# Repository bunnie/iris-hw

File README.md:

# IRIS CAD files

This repository contains IRIS CAD files not found elsewhere.

In particular, the base machine is the [Jubilee3D](https://jubilee3d.com/index.php?title=Main_Page); please refer to its [github](https://github.com/machineagency/jubilee) for its base CAD files.

## About IRIS

This repository is part of the IRIS project, an effort to make it easier to verify the construction of silicon chips.

Read more about IRIS at our [arXiv paper](https://arxiv.org/abs/2303.07406), or the latest [project update](https://www.bunniestudios.com/blog/?p=6937).

## Acknowledgements

This work was funded in part by NLnet’s [NGI0 Entrust](https://nlnet.nl/entrust/) fund, established with support from the European Commission’s Next Generation Internet Program, and my [Github Sponsors](https://github.com/sponsors/bunnie/).

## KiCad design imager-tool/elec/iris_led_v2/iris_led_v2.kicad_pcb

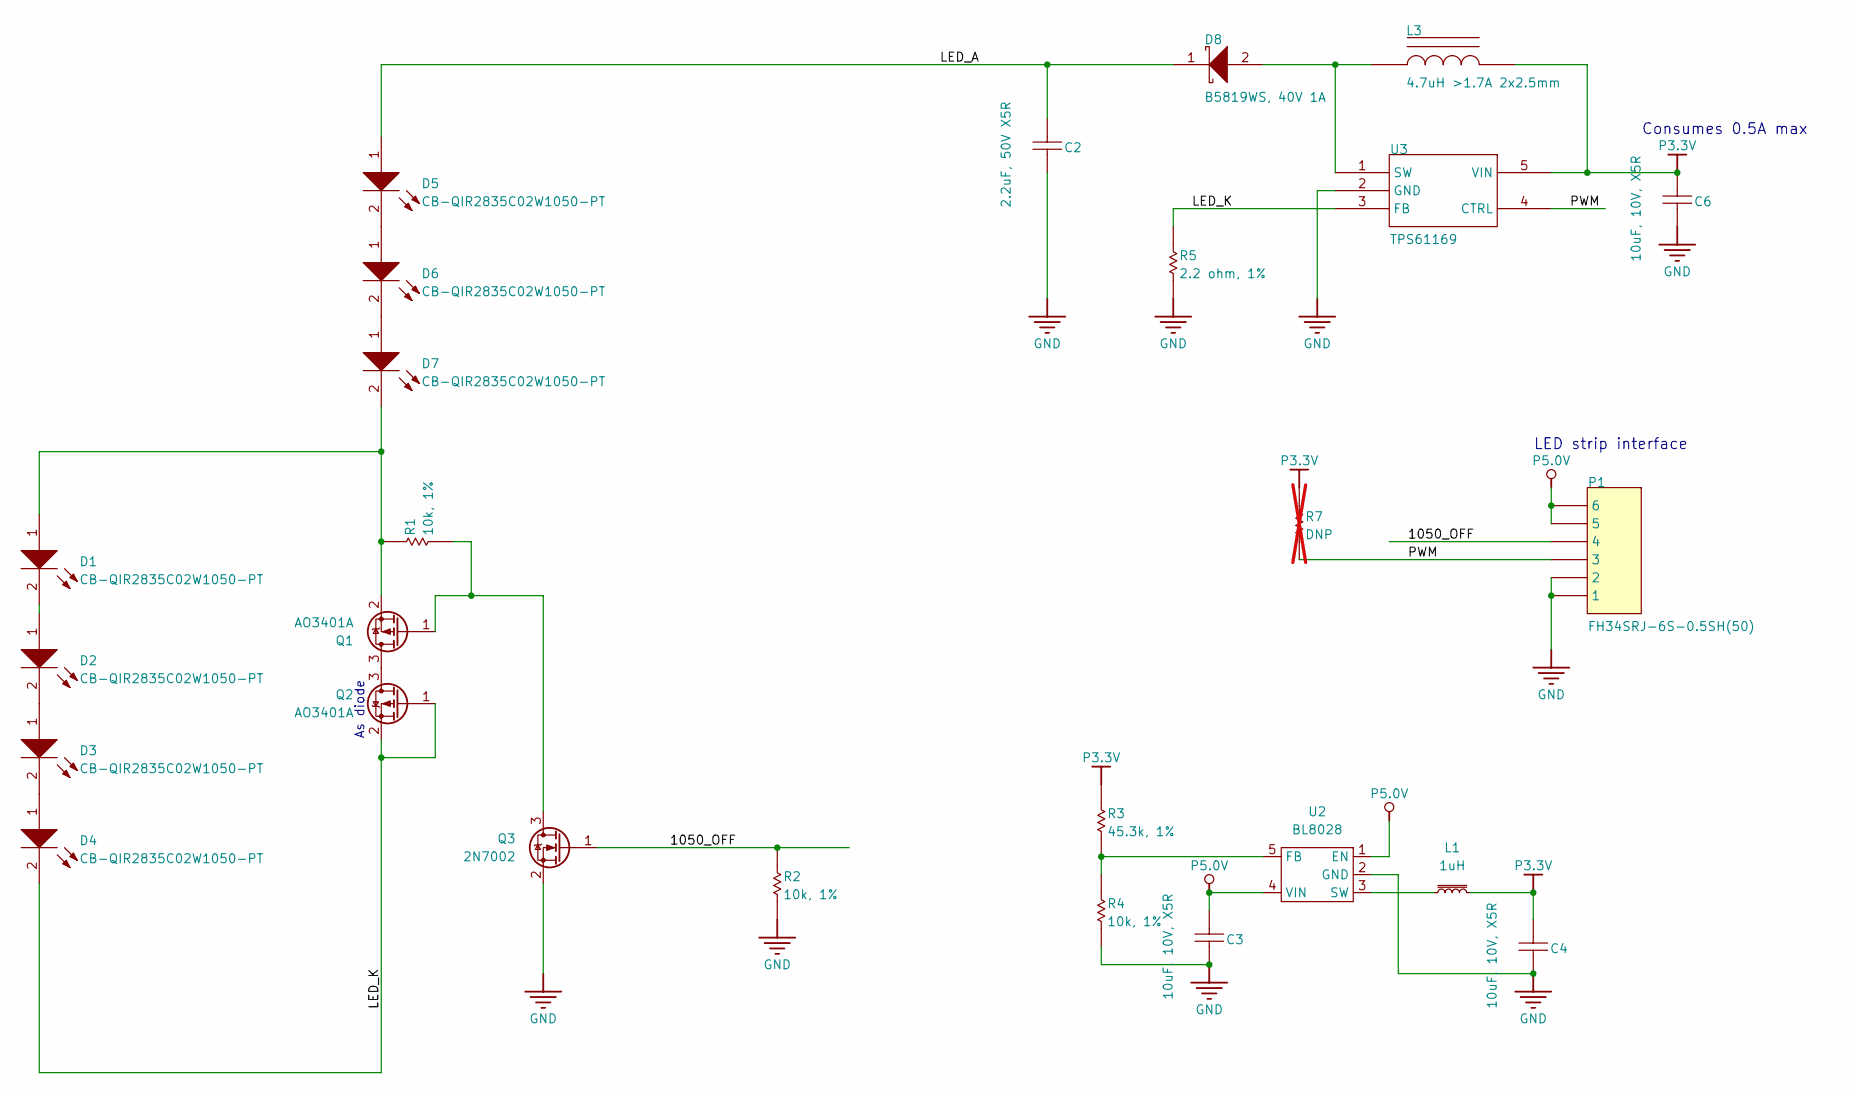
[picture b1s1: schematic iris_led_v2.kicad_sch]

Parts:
C2: 2.2uF, 50V X5R; C_0805_2012Metric; MPN CL21A225KBQNNNE; JLCPCB C377773
C3, C4, C6: 10uF, 10V, X5R; C_0603_1608Metric; MPN CL10A106KP8NNNC; LCSC C19702
D1, D2, D3, D4, D5, D6, D7: CB-QIR2835C02W1050-PT; LED_PLCC_2835; MPN CB-QIR2835C02W1050-PT
D8: B5819WS, 40V 1A; D_SOD-323; MPN B5819WS; LCSC C7420331
L1: 1uH; L_1008_2520Metric; LCSC C435392
L3: 4.7uH >1.7A 2x2.5mm; L_Changjiang_FNR252010S; MPN FTC252010S4R7MBCA; LCSC C5832360
P1: FH34SRJ-6S-0.5SH(50); HRS_FH34SRJ-6S-0.5SH(50); MPN FH34SRJ-6S-0.5SH(50); LCSC C5213748
Q1, Q2: AO3401A; SOT-23
Q3: 2N7002; SOT-23; LCSC C8545
R1, R2, R4: 10k, 1%; R_0402_1005Metric; MPN ANY; LCSC C25744
R3: 45.3k, 1%; R_0402_1005Metric; MPN ANY; LCSC C137977
R5: 2.2 ohm, 1%; R_0603_1608Metric; MPN RC0603FR-7W2R2L; LCSC C22939
R7: DNP; R_0402_1005Metric; MPN DNP; not fitted
U2: BL8028; SOT-23-5; LCSC C266177
U3: TPS61169; SOT-353_SC-70-5; MPN TPS61169DCKR; LCSC C71045

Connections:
/1050_OFF: P1.4, Q3.1 (G), R2.2
/LED_A: C2.1, D5.1 (A), D8.1 (K)
/LED_K: D4.2 (K), Q2.1 (G), Q2.2 (S), R5.1, U3.3 (FB)
/PWM: P1.3, R7.2, U3.4 (CTRL)
GND: C2.2, C3.2, C4.2, C6.2, P1.1, P1.2, Q3.2 (S), R2.1, R4.1, R5.2, U2.2 (GND), U3.2 (GND)
unnamed: D1.1 (A), D7.2 (K), Q1.2 (S), R1.2
unnamed: D1.2 (K), D2.1 (A)
unnamed: D2.2 (K), D3.1 (A)
unnamed: D3.2 (K), D4.1 (A)
unnamed: D5.2 (K), D6.1 (A)
unnamed: D6.2 (K), D7.1 (A)
unnamed: D8.2 (A), L3.1, U3.1 (SW)
unnamed: Q1.3 (D), Q2.3 (D)
unnamed: Q1.1 (G), Q3.3 (D), R1.1
unnamed: R3.1, R4.2, U2.5 (FB)
unnamed: L1.1, U2.3 (SW)
P3.3V: C4.1, C6.1, L1.2, L3.2, R3.2, R7.1, U3.5 (VIN)
P5.0V: C3.1, P1.5, P1.6, U2.1 (EN), U2.4 (VIN)

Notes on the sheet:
Consumes 0.5A max
As diode
LED strip interface

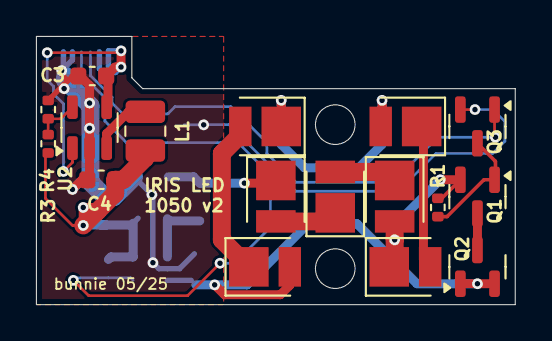
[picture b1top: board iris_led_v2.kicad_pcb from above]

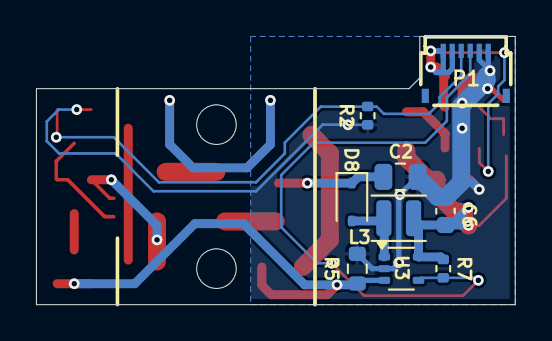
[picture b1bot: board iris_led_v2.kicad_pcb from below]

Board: 2 copper layers, 26.6 x 14.9 mm, 26 parts (9 on the bottom side), 18 nets.

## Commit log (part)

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2024-03-04 make the repo
2024-03-04 add boilerplate
2024-03-04 add piezo stage files
2024-03-04 add more iris design files
2024-03-04 add remaining design files
2024-03-10 add an about and acknowledgments
2024-03-17 add logo
2025-05-02 exploration & prototyping of alternate mountings
    A square mounting plate makes it easier to align samples
    to the IRIS system.
    Two variants are included here
    - "square" is designated for direct chip mounts, for generating
    reference images
    - "qsuare-1d" is designated for system-level mounts. it also
2025-05-02 add laser driver and mount
2025-05-02 add readme for laser
